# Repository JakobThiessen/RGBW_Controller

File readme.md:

# Hardware

| Top side                |Bottom side              |
|-----------------------:|:-------------------------:|
|  |  |

## Version mit PCA9685

4 x Input
2 x RGBW
1 x 1-Wire

# Software

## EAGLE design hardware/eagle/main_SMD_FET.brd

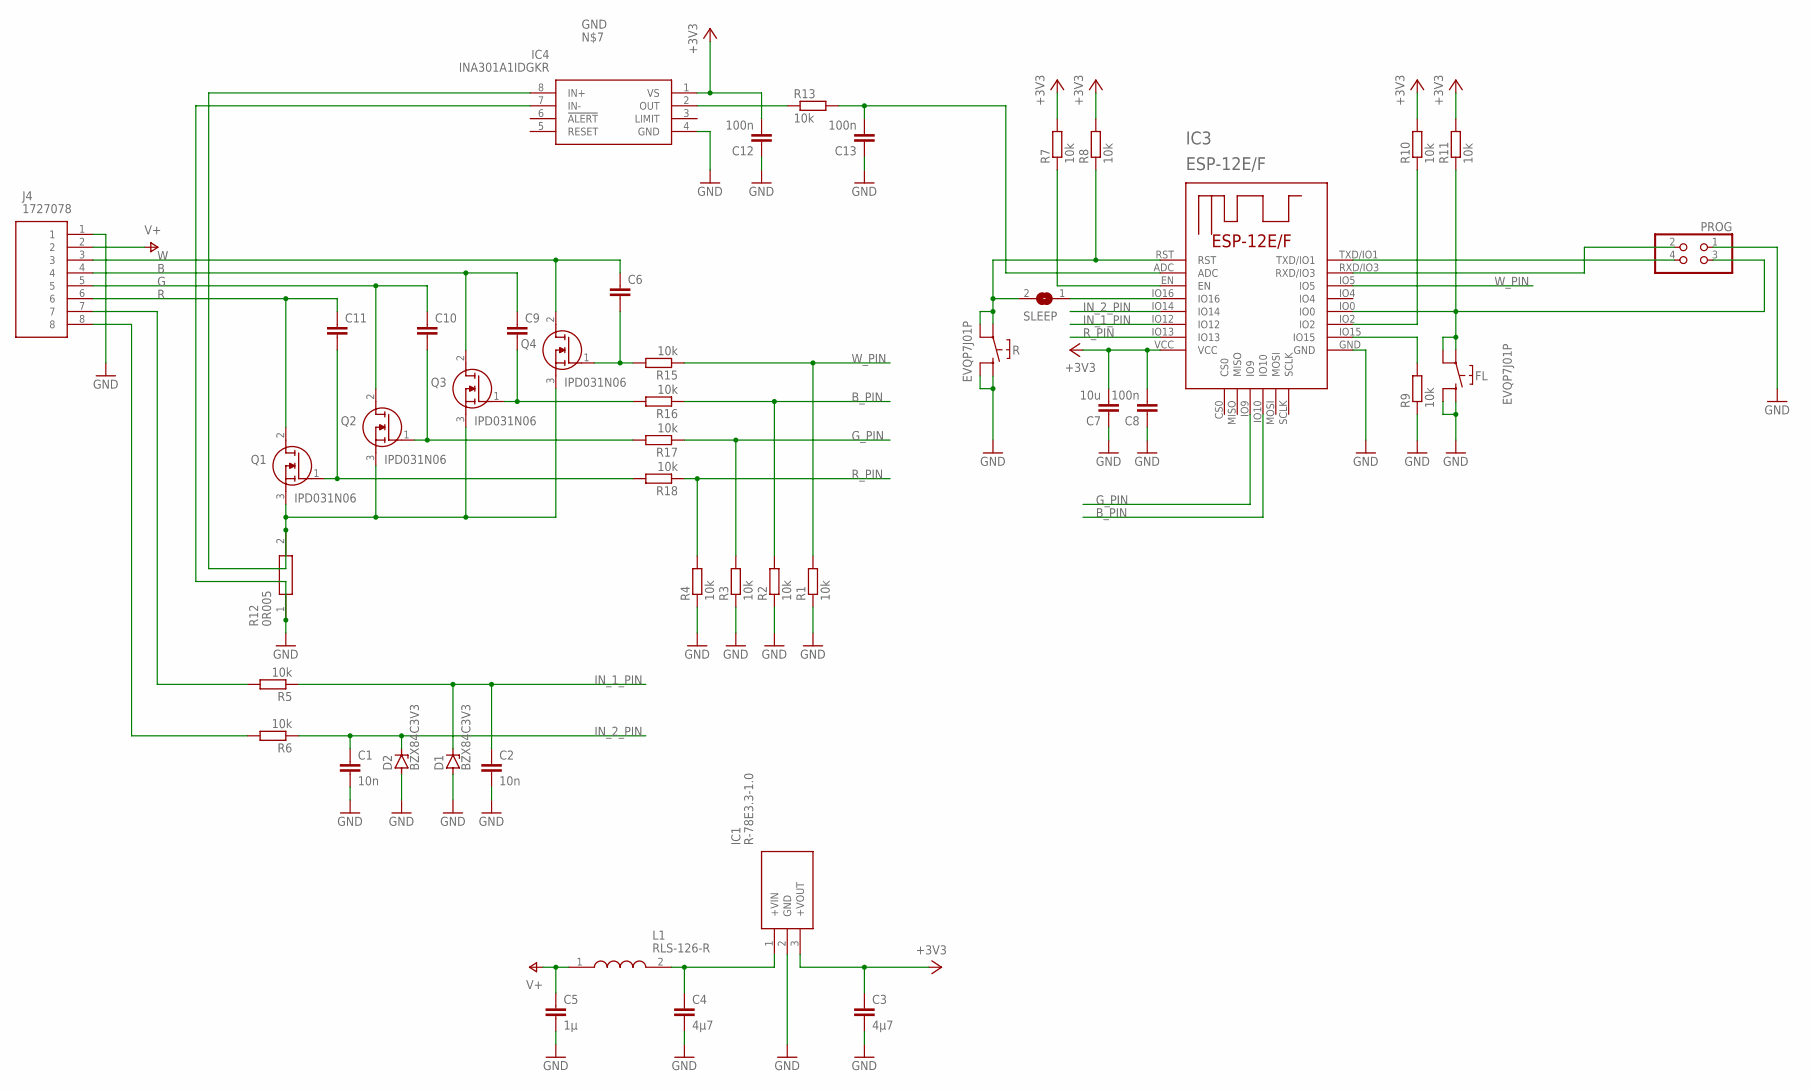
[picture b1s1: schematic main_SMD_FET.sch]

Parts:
C1, C2: 10n; C0603
C3: 4µ7; C0603
C4: 4µ7; C1206
C5: 1µ; C1206
C6, C9, C10, C11: C-EUC0402; C0402
C7: 10u; C0603
C8, C12, C13: 100n; C0603
D1, D2: BZX84C3V3; TO236
FL: EVQP7J01P
IC1: R-78E3.3-1.0; R78E3310
IC3: ESP-12E/F; ESP-12E
IC4: INA301A1IDGKR; SOP65P490X110-8N
J4: 1727078; SHDR8W90P0X381_1X8_3047X730X86
L1: RLS-126-R; RLS126R
PROG: PINHD-2X2; 2X02
Q1, Q2, Q3, Q4: IPD031N06; IPD031N06L3GATMA1
R: EVQP7J01P
R1, R2, R3, R4, R7, R8, R9, R10, R11, R13, R15, R16, R17, R18: 10k; R0402
R5, R6: 10k; R0603
R12: 0R005; RESC3216X68N
SLEEP: SJ

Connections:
+3V3: C3.1, C7.2, C8.2, C12.2, IC1.3 (+VOUT), IC3.VCC, IC4.1 (VS), R7.2, R8.2, R10.2, R11.2
B: C9.1, J4.4, Q3.2 (D)
B_PIN: IC3.IO10, R2.2, R16.1
G: C10.1, J4.5, Q2.2 (D)
GND: C1.2, C2.2, C3.2, C4.2, C5.2, C7.1, C8.1, C12.1, C13.1, D1.A, D2.A, FL.A2 (COM_1), FL.B2 (COM_2), IC1.2 (GND), IC3.GND, IC4.4 (GND), IC4.7 (IN-), J4.1, PROG.1, R.A2 (COM_1), R.B2 (COM_2), R1.1, R2.1, R3.1, R4.1, R9.1, R12.1
G_PIN: IC3.IO9, R3.2, R17.1
IN_1_PIN: C2.1, D1.C, IC3.IO12, R5.1
IN_2_PIN: C1.1, D2.C, IC3.IO14, R6.1
N$: C13.2, IC3.ADC, R13.2
unnamed: C11.2, Q1.1 (G), R18.2
unnamed: IC3.RST, R.A1 (NO_1), R.B1 (NO_2), R8.1, SLEEP.2
unnamed: J4.7, R5.2
unnamed: J4.8, R6.2
unnamed: IC3.RXD/IO3, PROG.2
unnamed: IC4.8 (IN+), Q1.3 (S), Q2.3 (S), Q3.3 (S), Q4.3 (S), R12.2
unnamed: IC4.2 (OUT), R13.1
unnamed: C4.1, IC1.1 (+VIN), L1.2
unnamed: IC3.EN, R7.1
unnamed: IC3.IO2, R10.1
unnamed: C10.2, Q2.1 (G), R17.2
unnamed: FL.A1 (NO_1), FL.B1 (NO_2), IC3.IO0, PROG.3, R11.1
unnamed: C9.2, Q3.1 (G), R16.2
unnamed: C6.2, Q4.1 (G), R15.2
unnamed: IC3.TXD/IO1, PROG.4
unnamed: IC3.IO16, SLEEP.1
unnamed: IC3.IO15, R9.2
R: C11.1, J4.6, Q1.2 (D)
R_PIN: IC3.IO13, R4.2, R18.1
V+: C5.1, J4.2, L1.1
W: C6.1, J4.3, Q4.2 (D)
W_PIN: IC3.IO5, R1.2, R15.1

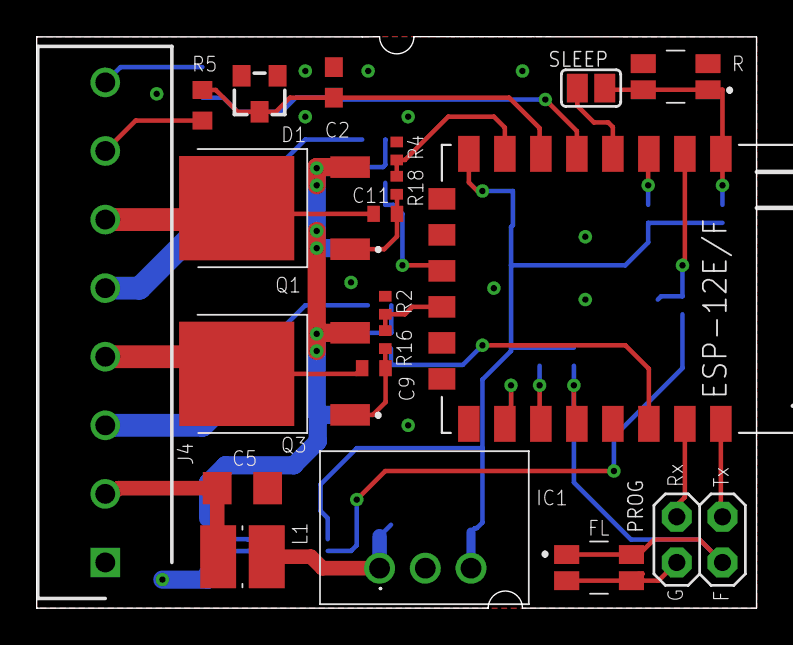
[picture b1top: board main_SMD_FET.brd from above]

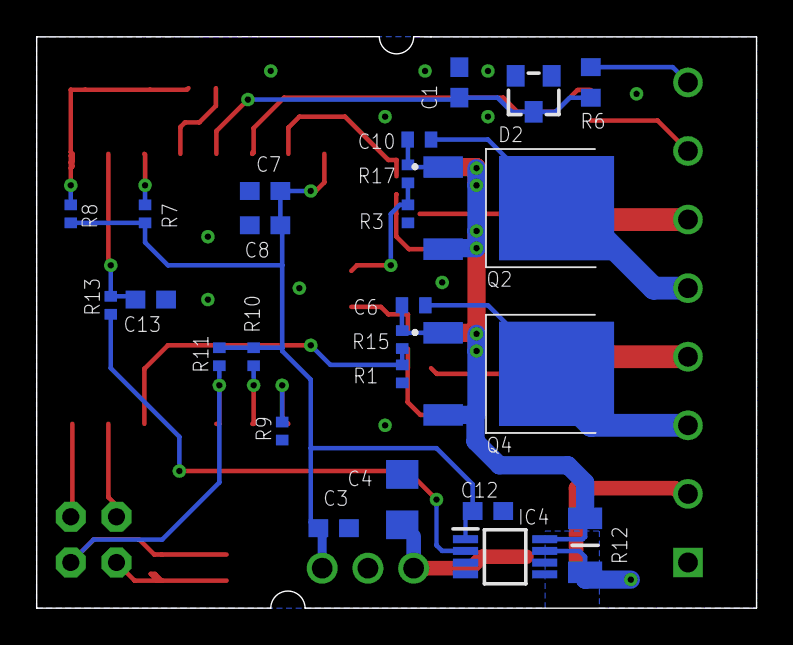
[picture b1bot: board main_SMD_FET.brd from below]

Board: 2 copper layers, 40.0 x 31.8 mm, 45 parts (25 on the bottom side), 31 nets.

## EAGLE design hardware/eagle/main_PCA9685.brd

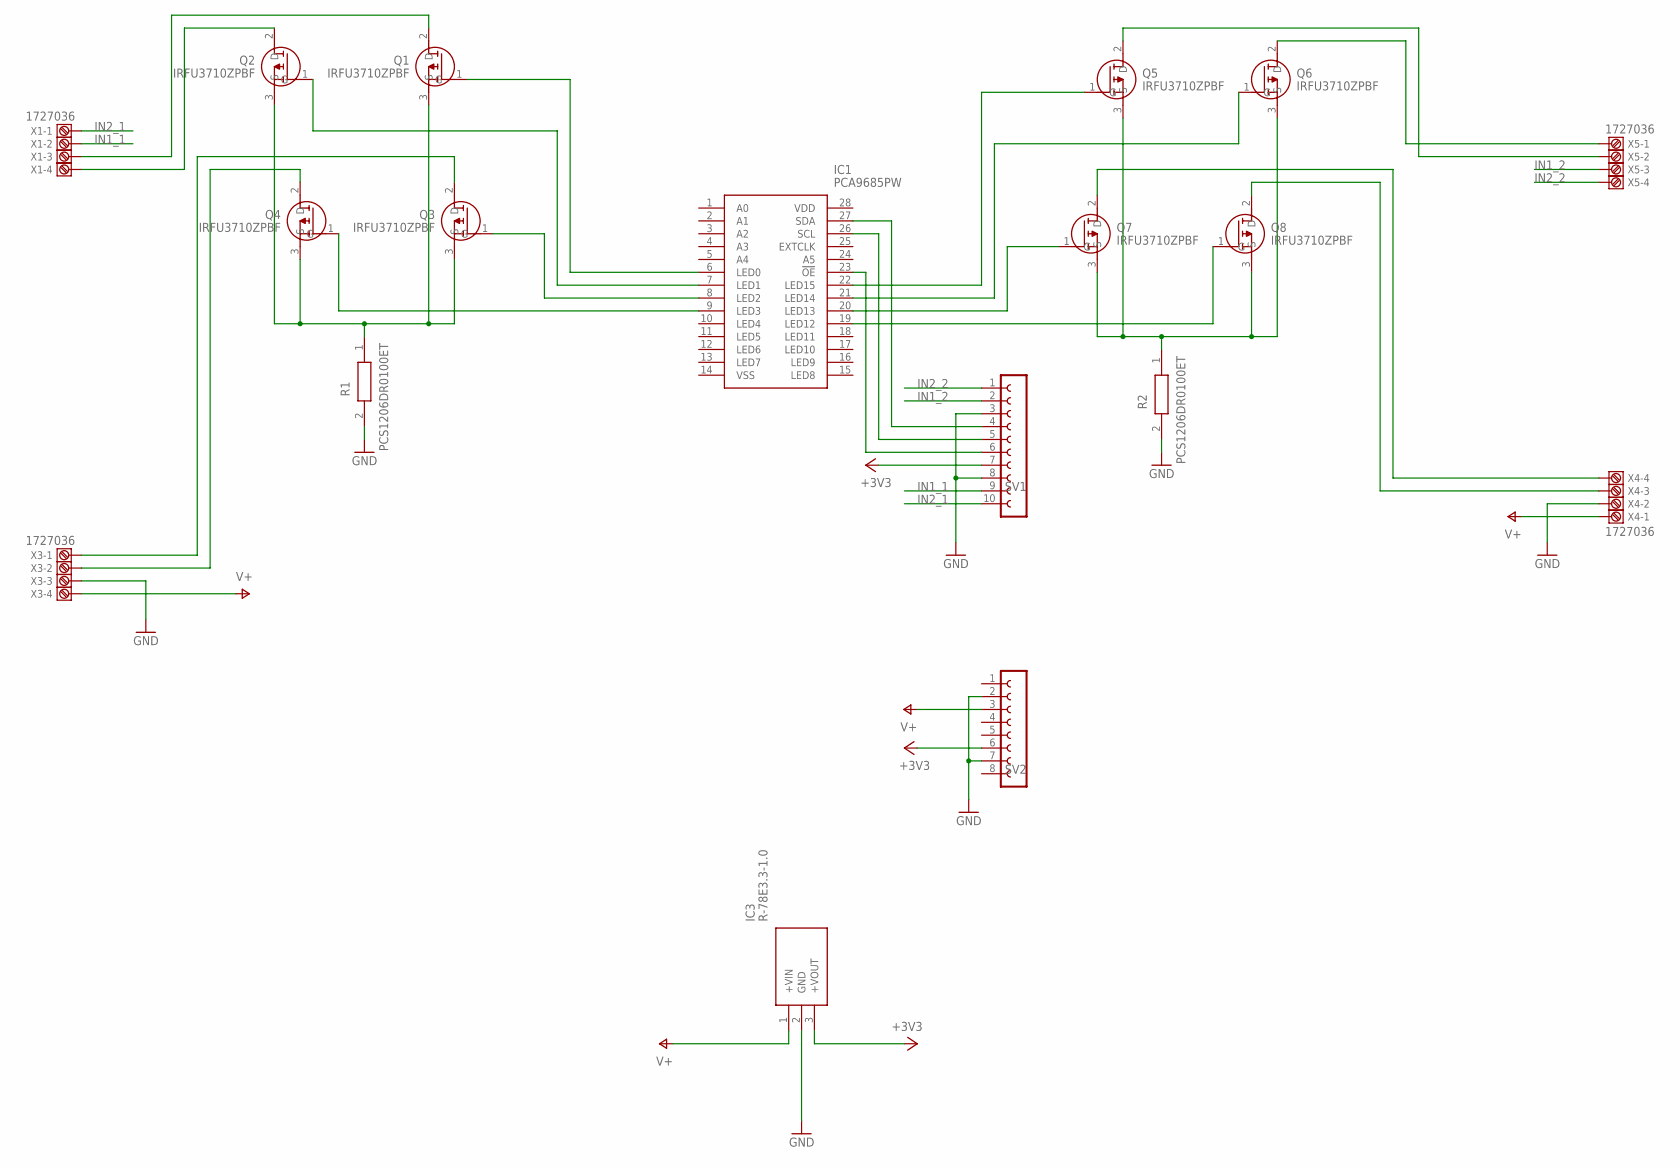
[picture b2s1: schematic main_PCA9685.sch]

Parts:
IC1: PCA9685PW; SOP65P640X110-28N
IC3: R-78E3.3-1.0; R78E3310
Q1, Q2, Q3, Q4, Q5, Q6, Q7, Q8: IRFU3710ZPBF; TO229P239X654X978-3P
R1, R2: PCS1206DR0100ET; RESC3216X68N
SV1: FE10-1; FE10
SV2: FE08-1; FE08
X1, X3, X4, X5: 1727036

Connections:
+3V3: IC3.3 (+VOUT), SV1.7, SV2.6
GND: IC3.2 (GND), R1.2, R2.2, SV1.3, SV1.8, SV2.2, SV2.7, X3.3, X4.2
IN1_1: SV1.9, X1.2
IN1_2: SV1.2, X5.3
IN2_1: SV1.10, X1.1
IN2_2: SV1.1, X5.4
unnamed: IC1.8 (LED2), Q3.1 (G)
unnamed: IC1.9 (LED3), Q4.1 (G)
unnamed: IC1.7 (LED1), Q2.1 (G)
unnamed: IC1.6 (LED0), Q1.1 (G)
unnamed: Q4.2 (D), X3.2
unnamed: Q3.2 (D), X3.1
unnamed: Q2.2 (D), X1.4
unnamed: Q1.2 (D), X1.3
unnamed: IC1.27 (SDA), SV1.4
unnamed: Q1.3 (S), Q2.3 (S), Q3.3 (S), Q4.3 (S), R1.1
unnamed: IC1.26 (SCL), SV1.5
unnamed: Q5.3 (S), Q6.3 (S), Q7.3 (S), Q8.3 (S), R2.1
unnamed: Q8.2 (D), X4.3
unnamed: Q7.2 (D), X4.4
unnamed: Q6.2 (D), X5.1
unnamed: Q5.2 (D), X5.2
unnamed: IC1.19 (LED12), Q8.1 (G)
unnamed: IC1.20 (LED13), Q7.1 (G)
unnamed: IC1.21 (LED14), Q6.1 (G)
unnamed: IC1.22 (LED15), Q5.1 (G)
unnamed: IC1.23 (!OE), SV1.6
V+: IC3.1 (+VIN), SV2.3, X3.4, X4.1

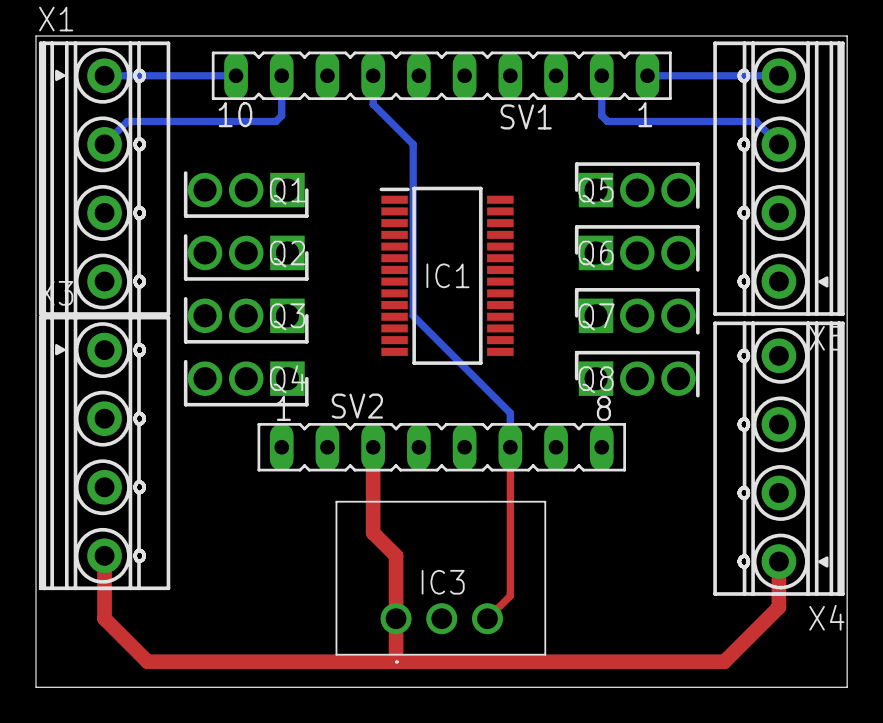
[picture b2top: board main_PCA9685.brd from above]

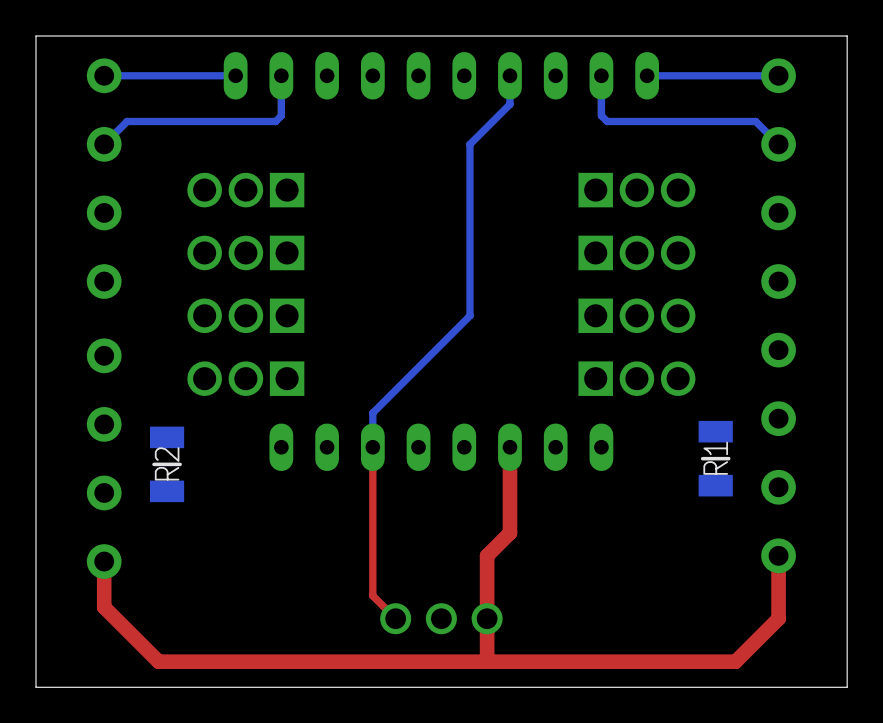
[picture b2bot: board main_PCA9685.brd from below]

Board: 2 copper layers, 45.1 x 36.2 mm, 18 parts (2 on the bottom side), 28 nets.

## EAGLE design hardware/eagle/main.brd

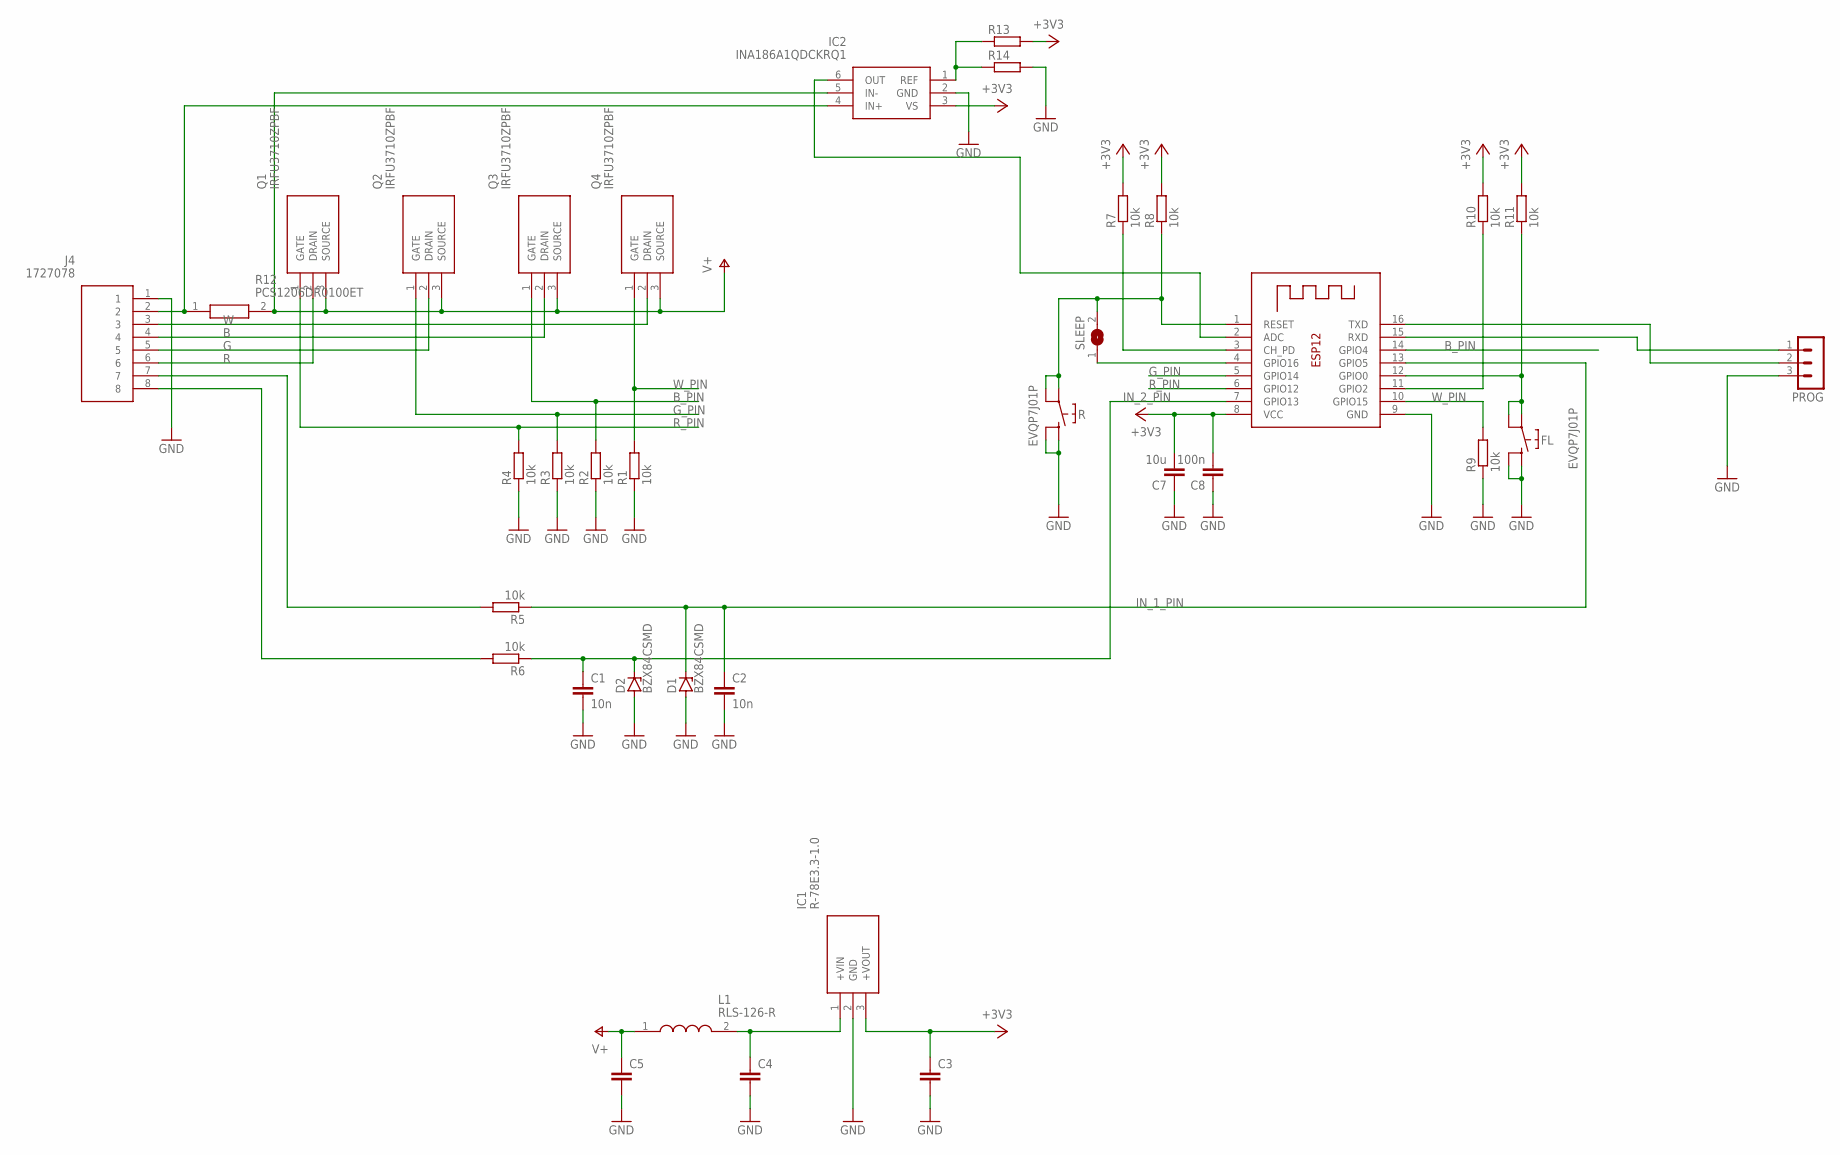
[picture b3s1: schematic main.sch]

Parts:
C1, C2: 10n; C0603
C3: C-EUC0603; C0603
C4, C5: C-EUC1206; C1206
C7: 10u; C0603
C8: 100n; C0603
D1, D2: BZX84CSMD; TO236
FL: EVQP7J01P
IC1: R-78E3.3-1.0; R78E3310
IC2: INA186A1QDCKRQ1; SOP65P210X110-6N
J4: 1727078; SHDR8W90P0X381_1X8_3047X730X86
L1: RLS-126-R; RLS126R
PROG: MA03-1
Q1, Q2, Q3, Q4: IRFU3710ZPBF; TO229P239X654X978-3P
R: EVQP7J01P
R1, R2, R3, R4, R5, R6, R7, R8, R9, R10, R11: 10k; R0603
R12: PCS1206DR0100ET; RESC3216X68N
R13, R14: R-EU_R0402; R0402
SLEEP: SJ
X2: ESP-12

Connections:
+3V3: C3.1, C7.2, C8.2, IC1.3 (+VOUT), IC2.3 (VS), R7.2, R8.2, R10.2, R11.2, R13.2, X2.8 (VCC)
B: J4.4, Q3.2 (DRAIN)
B_PIN: Q3.1 (GATE), R2.2, X2.14 (GPIO4)
G: J4.5, Q2.2 (DRAIN)
GND: C1.2, C2.2, C3.2, C4.2, C5.2, C7.1, C8.1, D1.A, D2.A, FL.A2 (COM_1), FL.B2 (COM_2), IC1.2 (GND), IC2.2 (GND), J4.1, PROG.3, R.A2 (COM_1), R.B2 (COM_2), R1.1, R2.1, R3.1, R4.1, R9.1, R14.2, X2.9 (GND)
G_PIN: Q2.1 (GATE), R3.2, X2.5 (GPIO14)
IN_1_PIN: C2.1, D1.C, R5.1, X2.13 (GPIO5)
IN_2_PIN: C1.1, D2.C, R6.1, X2.7 (GPIO13)
unnamed: IC2.6 (OUT), X2.2 (ADC)
unnamed: R.A1 (NO_1), R.B1 (NO_2), R8.1, SLEEP.2, X2.1 (RESET)
unnamed: J4.7, R5.2
unnamed: J4.8, R6.2
unnamed: PROG.1, X2.15 (RXD)
unnamed: IC2.4 (IN+), J4.2, R12.1
unnamed: IC2.1 (REF), R13.1, R14.1
unnamed: C4.1, IC1.1 (+VIN), L1.2
unnamed: R7.1, X2.3 (CH_PD)
unnamed: R10.1, X2.11 (GPIO2)
unnamed: FL.A1 (NO_1), FL.B1 (NO_2), R11.1, X2.12 (GPIO0)
unnamed: PROG.2, X2.16 (TXD)
unnamed: SLEEP.1, X2.4 (GPIO16)
R: J4.6, Q1.2 (DRAIN)
R_PIN: Q1.1 (GATE), R4.2, X2.6 (GPIO12)
V+: C5.1, IC2.5 (IN-), L1.1, Q1.3 (SOURCE), Q2.3 (SOURCE), Q3.3 (SOURCE), Q4.3 (SOURCE), R12.2
W: J4.3, Q4.2 (DRAIN)
W_PIN: Q4.1 (GATE), R1.2, R9.2, X2.10 (GPIO15)

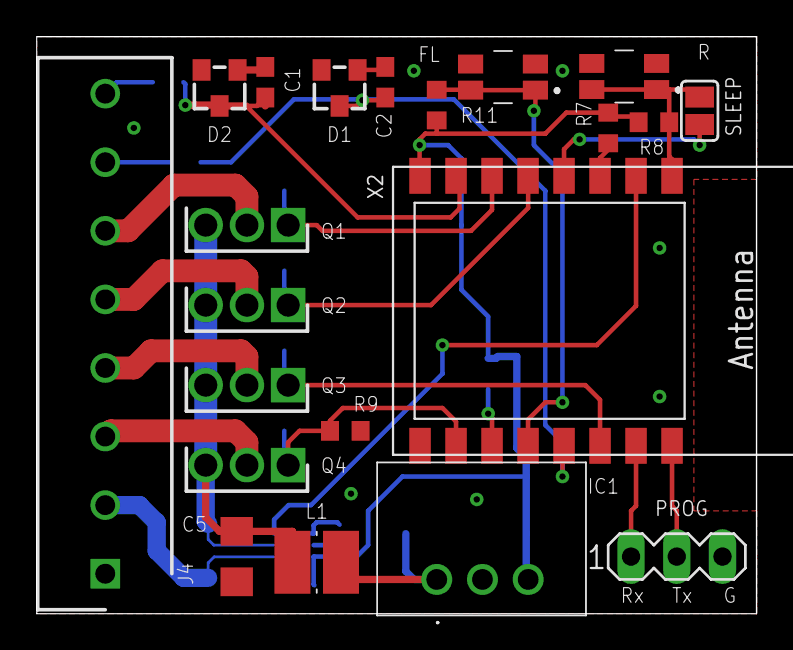
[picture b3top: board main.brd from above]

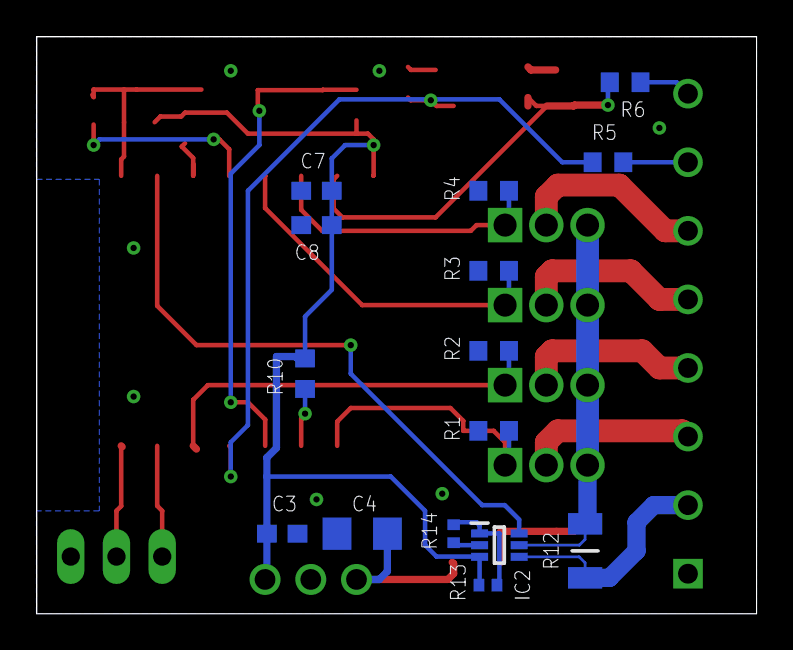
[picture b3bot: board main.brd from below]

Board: 2 copper layers, 40.0 x 32.1 mm, 36 parts (15 on the bottom side), 26 nets.

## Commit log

2021-02-07 init
2021-02-07 anpassungen
2021-02-07 intial
2021-02-07 initial
2021-02-07 Diagram.drawio
2021-02-24 Konturanpassung
2021-02-24 kleine Änderungen
2021-02-24 Dokumentation erstellt
2021-02-25 Set theme jekyll-theme-midnight
2021-03-01 tiefpass eingefügt. Leiterbahn etwas breiter für DC/DC wandler
2021-03-02 dokumentation
2021-03-02 Create gerb. data
2021-03-02 create pictures and 3D model (step format)
2021-03-17 Create tasmota_templates
